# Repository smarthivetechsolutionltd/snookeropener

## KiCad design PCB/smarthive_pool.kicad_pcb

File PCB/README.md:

# SmartHive Pool Opener - Main Controller PCB (V2.0 ESP32 DevKit V1)

Custom PCB for the SmartHive Snooker/Pool Table Ball Release & RFID Authentication System, upgraded from ESP8266 to the **ESP32 DevKit V1 (30-pin)** and high-torque **MG996R servo**.

---

## 1. Specifications

| Parameter | Value |
| :--- | :--- |
| **Dimensions** | 76.2 mm × 53.34 mm (3.0" × 2.1") |
| **Layers** | 2-Layer (FR-4, 1.6 mm thickness, 1 oz copper) |
| **MCU Socket** | ESP32 DevKit V1 (30-Pin, 25.4 mm / 1.0" row pitch) |
| **Power Input** | 5V DC via 5.08 mm screw terminal / header (from RFID Pod USB-C & slide switch) |
| **Reverse Polarity Protection** | SS34 / 1N5819 Schottky Diode (3A) |
| **Servo Power Rail** | Dedicated 5V high-current trace with **470 µF 25V** bulk electrolytic + 100 nF ceramic |
| **Mounting Holes** | 4× M2.5 mounting holes (68.2 mm × 45.34 mm hole spacing) |
| **Manufacturing Package** | Standard JLCPCB / PCBWay ready zip ([smarthive_pool_gerbers.zip](file:///Users/user/Documents/Projects/arduino/snookeropener/PCB/smarthive_pool_gerbers.zip)) |

---

## 2. Pin Connections & Wiring Mapping

### ESP32 DevKit V1 (30-Pin)

| ESP32 Pin | GPIO | Function | Destination Component / Header |
| :--- | :--- | :--- | :--- |
| **VIN** | - | 5V Power In | From 5V Rail (protected by SS34 diode) |
| **GND** | - | System Ground | Common Ground Plane |
| **3V3** | - | 3.3V Power Out | Power to MFRC522 RFID & 3.3V Power LED |
| **GPIO 18** | IO18 | Hardware VSPI SCK | `J2` RFID Pin 7 (SCK) |
| **GPIO 19** | IO19 | Hardware VSPI MISO | `J2` RFID Pin 6 (MISO) |
| **GPIO 23** | IO23 | Hardware VSPI MOSI | `J2` RFID Pin 5 (MOSI) |
| **GPIO 5** | IO5 | Hardware VSPI SS / SDA | `J2` RFID Pin 1 (SDA) |
| **GPIO 22** | IO22 | RFID Hard Reset | `J2` RFID Pin 2 (RST) |
| **GPIO 13** | IO13 | Hardware PWM Servo Signal | `J3` MG996R Servo Pin 3 (Signal) |
| **GPIO 26** | IO26 | Red LED PWM | `J6` HW-479 RGB Module Pin 2 (Red) |
| **GPIO 27** | IO27 | Green LED PWM | `J6` HW-479 RGB Module Pin 3 (Green) |
| **GPIO 32** | IO32 | Manual Release / Bench Test | `SW1` Tactile Pushbutton (Internal Pull-Up) |

---

## 3. Peripheral Connectors

1. **`J5` - 5V Power Terminal (2-Pin 5.08 mm pitch):**
   - Pin 1: `+5V` (Switched 5V from SS-12D00 slide switch)
   - Pin 2: `GND`
2. **`J3` - MG996R Servo Header (1×3 Pin 2.54 mm pitch):**
   - Pin 1: `GND` (Brown / Black)
   - Pin 2: `5V` (Red) — Buffered by 470 µF 25V capacitor
   - Pin 3: `SIG` (Orange / White) — Connected to ESP32 GPIO 13
3. **`J2` - RC522 RFID Header (1×8 Pin 2.54 mm pitch):**
   - Pin 1: `SDA` (GPIO 5)
   - Pin 2: `RST` (GPIO 22)
   - Pin 3: `3V3` (From ESP32 3V3 regulator)
   - Pin 4: `GND`
   - Pin 5: `MOSI` (GPIO 23)
   - Pin 6: `MISO` (GPIO 19)
   - Pin 7: `SCK` (GPIO 18)
   - Pin 8: `IRQ` (N/C)
4. **`J6` - HW-479 RGB LED Module Header (1×4 Pin 2.54 mm pitch):**
   - Pin 1: `GND` (Cathode)
   - Pin 2: `RED` (GPIO 26)
   - Pin 3: `GREEN` (GPIO 27)
   - Pin 4: `BLUE` (Optional / N/C)
5. **`SW1` - Bench Test Button (6×6 mm Tactile Button):**
   - Triggers ball release manually without needing an RFID card during servicing or installation.

---

## 4. Production Files

- **Gerbers & Drill Package:** [`smarthive_pool_gerbers.zip`](file:///Users/user/Documents/Projects/arduino/snookeropener/PCB/smarthive_pool_gerbers.zip)
- **Bill of Materials:** [`smarthive_pool_bom.csv`](file:///Users/user/Documents/Projects/arduino/snookeropener/PCB/smarthive_pool_bom.csv)
- **KiCad PCB Layout:** [`smarthive_pool.kicad_pcb`](file:///Users/user/Documents/Projects/arduino/snookeropener/PCB/smarthive_pool.kicad_pcb)
- **KiCad Schematic:** [`smarthive_pool.kicad_sch`](file:///Users/user/Documents/Projects/arduino/snookeropener/PCB/smarthive_pool.kicad_sch)
- **3D Render (Isometric):** [`pcb_render_3d_isometric.png`](file:///Users/user/Documents/Projects/arduino/snookeropener/PCB/pcb_render_3d_isometric.png)
- **3D Render (Top View):** [`pcb_render_3d_top.png`](file:///Users/user/Documents/Projects/arduino/snookeropener/PCB/pcb_render_3d_top.png)
- **3D Render (Bottom View):** [`pcb_render_3d_bottom.png`](file:///Users/user/Documents/Projects/arduino/snookeropener/PCB/pcb_render_3d_bottom.png)

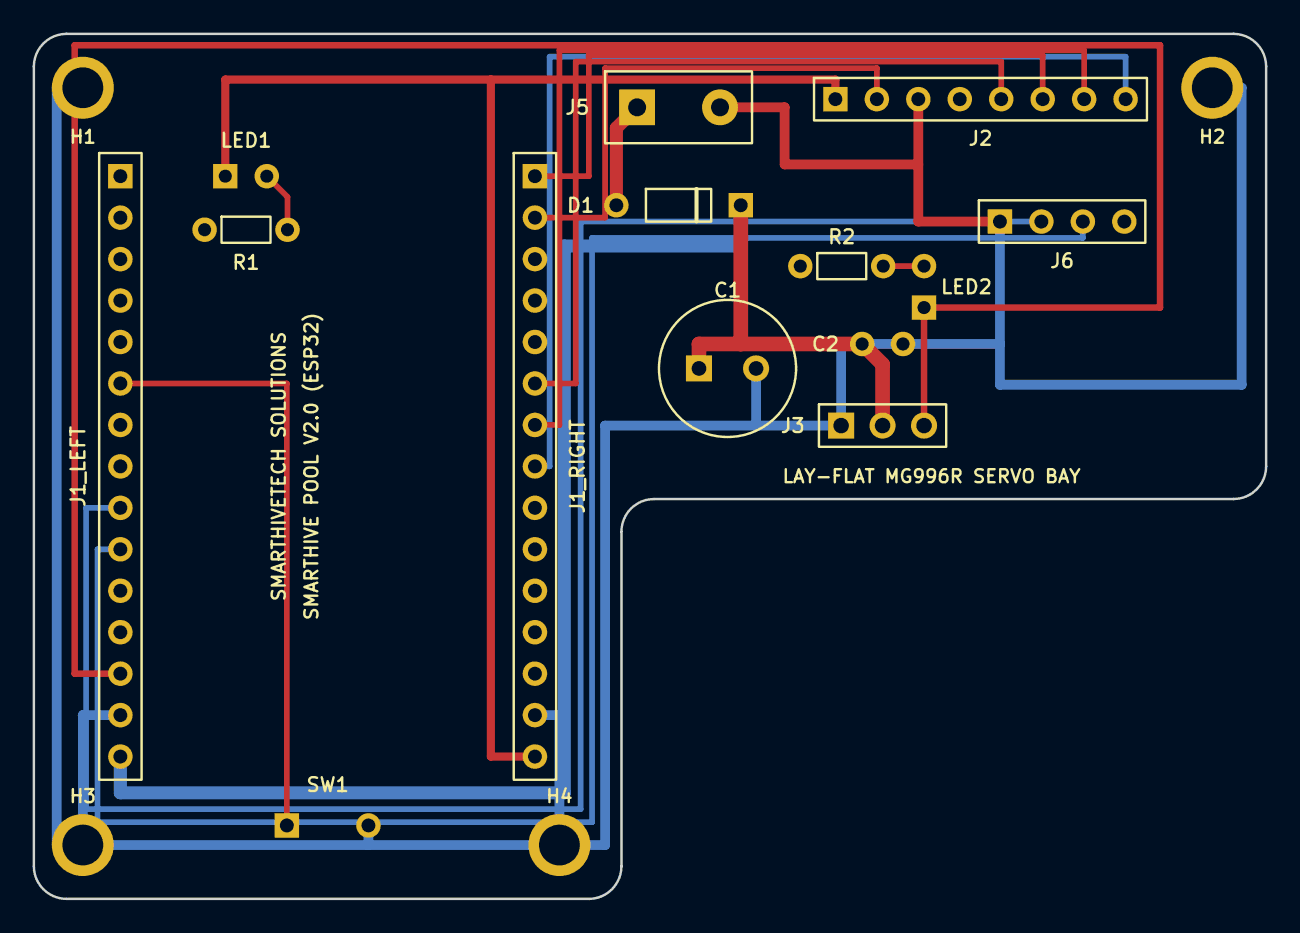
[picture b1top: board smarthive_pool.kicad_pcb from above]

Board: 2 copper layers, 75.5 x 53.0 mm, 18 parts (0 on the bottom side), 15 nets.

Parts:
C1: 470uF_25V; CP_Radial_D8.0mm_P3.50mm
C2: 100nF; C_Disc_D4.7mm_W2.6mm_P2.50mm
D1: SS34/1N5819; D_DO-41_SOD81_P7.62mm_Horizontal
H1, H2, H3, H4: M2.5_Mount; MountingHole_2.5mm_M2.5_Pad
J1_LEFT: ESP32_GPIO_LEFT; PinSocket_1x15_P2.54mm_Vertical
J1_RIGHT: ESP32_GPIO_RIGHT; PinSocket_1x15_P2.54mm_Vertical
J2: RC522_RFID; PinHeader_1x08_P2.54mm_Vertical
J3: MG996R_SERVO; PinHeader_1x03_P2.54mm_Vertical
J5: USB_C_SW_5V; TerminalBlock_bornier-2_P5.08mm
J6: HW479_RGB; PinHeader_1x04_P2.54mm_Vertical
LED1: 3V3_OK; LED_D3.0mm
LED2: SERVO_ON; LED_D3.0mm
R1, R2: 1k; R_Axial_DIN0207_L6.3mm_D2.5mm_P5.08mm_Horizontal
SW1: TEST_BTN; SW_PUSH_6mm

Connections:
+3V3: J1_RIGHT.15, J2.1, LED1.1
+5V: C1.1, C2.1, D1.2, J1_LEFT.15, J3.2
GND: C1.2, C2.2, H1.1, H2.1, H3.1, H4.1, J1_LEFT.14, J1_RIGHT.14, J2.3, J3.1, J5.2, J6.1, R1.2, R2.2, SW1.2
LED_GRN: J1_LEFT.10, J6.3
LED_RED: J1_LEFT.9, J6.2
NFC_MISO: J1_RIGHT.6, J2.5
NFC_MOSI: J1_RIGHT.1, J2.6
NFC_RST: J1_RIGHT.2, J2.2
NFC_SCK: J1_RIGHT.7, J2.7
NFC_SDA: J1_RIGHT.8, J2.8
unnamed: LED1.2, R1.1
unnamed: LED2.2, R2.1
SERVO_PWM: J1_LEFT.13, J3.3, LED2.1
TEST_BTN: J1_LEFT.6, SW1.1
VIN_SW: D1.1, J5.1

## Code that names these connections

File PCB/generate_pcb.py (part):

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    ("VN",       0,  ""),             # 3. GPIO 39
    ("D34",      0,  ""),             # 4. GPIO 34
    ("D35",      0,  ""),             # 5. GPIO 35
    ("D32_BTN",  10, "TEST_BTN"),     # 6. GPIO 32 -> Manual Test Button
    ("D33",      0,  ""),             # 7. GPIO 33
    ("D25",      0,  ""),             # 8. GPIO 25
    ("D26_RED",  12, "LED_RED"),      # 9. GPIO 26 -> RGB Red
    ("D27_GRN",  13, "LED_GRN"),      # 10. GPIO 27 -> RGB Green
    ("D14",      0,  ""),             # 11. GPIO 14
    ("D12",      0,  ""),             # 12. GPIO 12
    ("D13_SRV",  9,  "SERVO_PWM"),    # 13. GPIO 13 -> Servo PWM
    ("GND",      1,  "GND"),          # 14. GND
    ("VIN_5V",   2,  "+5V"),          # 15. VIN (+5V)
]

right_pins = [
    ("D23_MOSI", 8,  "NFC_MOSI"),     # 1. GPIO 23 -> VSPI MOSI
    ("D22_RST",  4,  "NFC_RST"),      # 2. GPIO 22 -> RC522 RST
    ("TX0",      0,  ""),             # 3. GPIO 1
    ("RX0",      0,  ""),             # 4. GPIO 3
    ("D21",      0,  ""),             # 5. GPIO 21
    ("D19_MISO", 7,  "NFC_MISO"),     # 6. GPIO 19 -> VSPI MISO
    ("D18_SCK",  6,  "NFC_SCK"),      # 7. GPIO 18 -> VSPI SCK
    ("D5_SDA",   5,  "NFC_SDA"),      # 8. GPIO 5  -> VSPI SS (SDA)
    ("TX2",      0,  ""),             # 9. GPIO 17
    ("RX2",      0,  ""),             # 10. GPIO 16
    ("D4",       0,  ""),             # 11. GPIO 4
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LED2,Amber 3mm,LED D3mm,1,Servo Ball Release Active Indicator,C965800
R1,1k Ohm,Axial DIN0207 P5.08mm,1,LED1 Current Limiter Resistor (1/4W),C25113
R2,1k Ohm,Axial DIN0207 P5.08mm,1,LED2 Current Limiter Resistor (1/4W),C25113
SW1,TEST_BTN,Tactile Switch 6x6mm 2-Pin,1,Onboard Bench Test / Manual Ball Release Pushbutton (GPIO 32),C318884
H1-H4,M2.5_Mount,2.5mm Hole 3.8mm Pad,4,Controller Enclosure Chassis Standoff Fasteners,Hardware
"""

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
